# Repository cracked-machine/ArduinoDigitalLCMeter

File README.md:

# ArduinoDigitalLCMeter
ArduinoNano-based Digital LC Meter with 2.42" OLED display

Based on this Silicon Chip magazine [article](Silicon Chip June 2017 p28-53.pdf)

### Schematic

https://github.com/cracked-machine/ArduinoDigitalLCMeter/blob/master/Hardware/docs/Digital_LC_Meter.pdf

### Layout

### Front Panel

### BOM

https://github.com/cracked-machine/ArduinoDigitalLCMeter/blob/master/Hardware/docs/Digital_LC_Meter.csv

* Carlingswitch Double Pole Double Throw (DPDT), Latching Rocker Switch Panel - Mfr. Part No. 621-1592900NXRS
* Marquardt Single Pole Double Throw (SPDT), (On)-Off-(On) Rocker Switch Panel - Mfr. Part No. 1808.1302
* APEM Single Pole Single Throw (SPST) Momentary Push Button Switch, Panel Mount - Mfr. Part No. 1213C RED
* www.diymore.cc 2.42" Inch 12864 OLED Display Module SSD1309

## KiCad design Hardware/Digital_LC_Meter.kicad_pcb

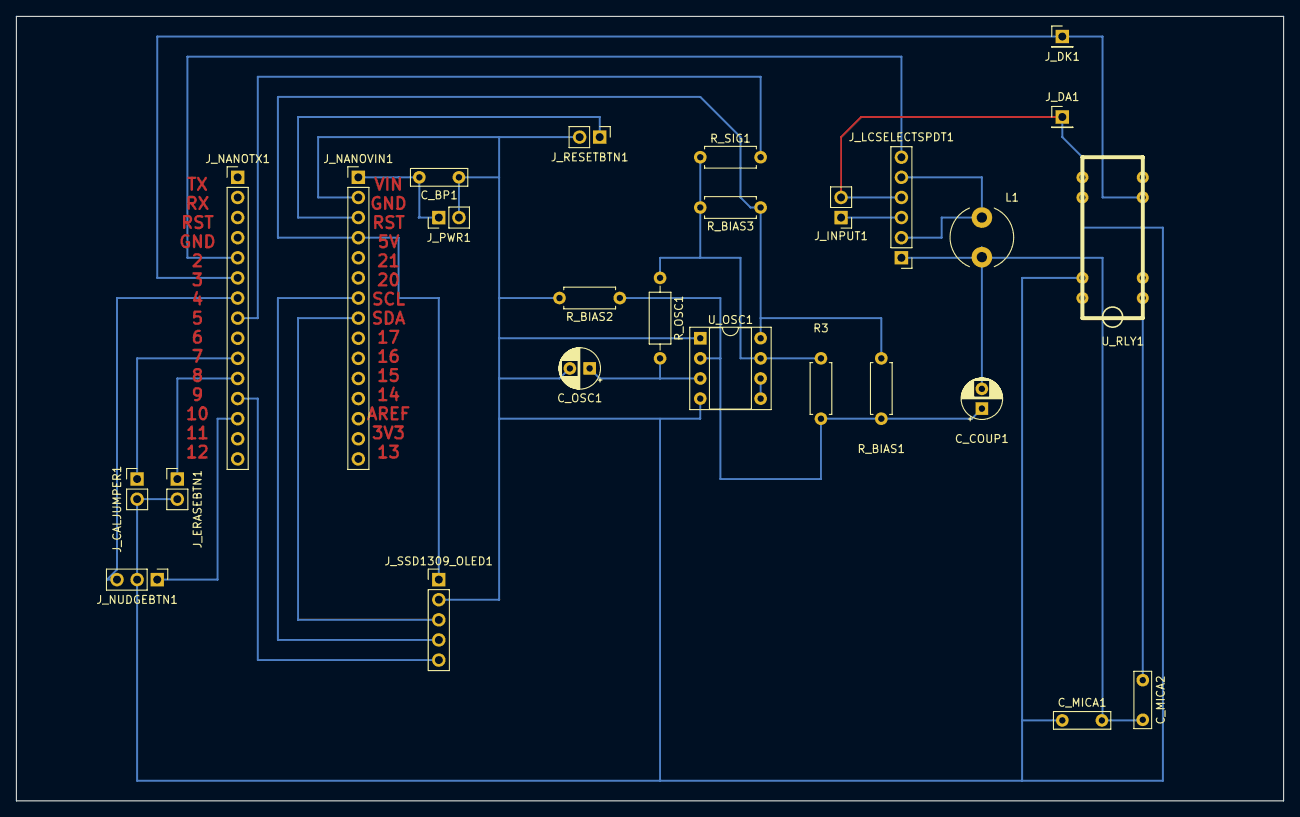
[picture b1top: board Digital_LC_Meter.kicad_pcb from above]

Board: 2 copper layers, 160.0 x 99.1 mm, 26 parts (0 on the bottom side), 22 nets.

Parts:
C_BP1: 100nF; C_Rect_L7.0mm_W2.0mm_P5.00mm
C_COUP1: 10uF; CP_Radial_D5.0mm_P2.50mm
C_MICA1, C_MICA2: 1nF; C_Rect_L7.0mm_W2.0mm_P5.00mm
C_OSC1: 10uF; CP_Radial_D5.0mm_P2.50mm
J_CALJUMPER1: Conn_01x02; PinHeader_1x02_P2.54mm_Vertical
J_DA1: Conn_01x01; PinHeader_1x01_P2.54mm_Vertical
J_DK1: Conn_01x01; PinHeader_1x01_P2.54mm_Vertical
J_ERASEBTN1: Conn_01x02; PinHeader_1x02_P2.54mm_Vertical
J_INPUT1: Conn_01x02; PinHeader_1x02_P2.54mm_Vertical
J_LCSELECTSPDT1: Conn_01x06; PinHeader_1x06_P2.54mm_Vertical
J_NANOTX1: Conn_01x15; PinHeader_1x15_P2.54mm_Vertical
J_NANOVIN1: Conn_01x15; PinHeader_1x15_P2.54mm_Vertical
J_NUDGEBTN1: Conn_01x03; PinHeader_1x03_P2.54mm_Vertical
J_PWR1: Conn_01x02; PinHeader_1x02_P2.54mm_Vertical
J_RESETBTN1: Conn_01x02; PinHeader_1x02_P2.54mm_Vertical
J_SSD1309_OLED1: Conn_01x05; PinHeader_1x05_P2.54mm_Vertical
L1: 100uH; L_Radial_D7.8mm_P5.00mm_Fastron_07HCP
R3: 100K; R_Axial_DIN0207_L6.3mm_D2.5mm_P7.62mm_Horizontal
R_BIAS1, R_BIAS2: 100K; R_Axial_DIN0207_L6.3mm_D2.5mm_P7.62mm_Horizontal
R_BIAS3: 4K7; R_Axial_DIN0207_L6.3mm_D2.5mm_P7.62mm_Horizontal
R_OSC1: 47K; R_Axial_DIN0207_L6.3mm_D2.5mm_P10.16mm_Horizontal
R_SIG1: 6K8; R_Axial_DIN0207_L6.3mm_D2.5mm_P7.62mm_Horizontal
U_OSC1: LM311; DIP-8_W7.62mm_Socket
U_RLY1: TE_ReedRelay_V23100V4xxxA010; TE_ReedRelay_V23100V4

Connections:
/5V: J_NANOVIN1.4, J_SSD1309_OLED1.1, R_BIAS1.1, R_BIAS3.1, U_OSC1.8
/CAL_ERASE_PIN8: J_ERASEBTN1.1, J_NANOTX1.11
/CAL_LK_PIN7: J_CALJUMPER1.1, J_NANOTX1.10
/CL_BAR_PIN2: J_LCSELECTSPDT1.6, J_NANOTX1.5
/DECR_PIN4: J_NANOTX1.7, J_NUDGEBTN1.3
/GND: C_BP1.1, C_MICA1.1, C_OSC1.2, J_CALJUMPER1.2, J_DA1.1, J_ERASEBTN1.2, J_INPUT1.2, J_LCSELECTSPDT1.4, J_NANOVIN1.2, J_NUDGEBTN1.2, J_PWR1.2, J_RESETBTN1.2, J_SSD1309_OLED1.2, R_BIAS2.2, U_OSC1.1, U_OSC1.4, U_RLY1.8, U_RLY1.9, U_RLY1.13
/INCR_PIN10: J_NANOTX1.13, J_NUDGEBTN1.1
/IND_PARALLEL: C_COUP1.2, C_MICA1.2, C_MICA2.2, J_LCSELECTSPDT1.1, L1.2
/IND_SERIES: J_LCSELECTSPDT1.2, J_LCSELECTSPDT1.5, L1.1
/OSC_SIG_PIN5: J_NANOTX1.8, R_SIG1.2
/RELAY_PIN3: J_DK1.1, J_NANOTX1.6, U_RLY1.6
/RESET_PIN: J_NANOVIN1.3, J_RESETBTN1.1
/SCL: J_NANOVIN1.7, J_SSD1309_OLED1.4
/SDA: J_NANOVIN1.8, J_SSD1309_OLED1.3
/SRST: J_NANOTX1.12, J_SSD1309_OLED1.5
/VIN: C_BP1.2, J_NANOVIN1.1, J_PWR1.1
unnamed: C_COUP1.1, R3.2, R_BIAS1.2, R_BIAS2.1, U_OSC1.2
unnamed: C_MICA2.1, U_RLY1.1
unnamed: C_OSC1.1, R_OSC1.2, U_OSC1.3
unnamed: J_INPUT1.1, J_LCSELECTSPDT1.3
unnamed: R3.1, R_BIAS3.2, R_OSC1.1, R_SIG1.1, U_OSC1.7
unnamed: U_OSC1.5, U_OSC1.6

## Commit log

2018-09-11 Converted schematic to KicadV5
2018-09-12 updated kicad files
2018-09-12 software update
2018-09-12 Added 2nd OLED and TCA9548A IICMux. Updated Schematic and Board Layouts
2018-09-14 updates
    - Added I2C Mux (TCA9548A) to design
    - Initial prototype tested (firmware needs work)
    - Created Front Panel Template for enclosure (Hammond 1455T1601)
2018-09-19 fixed OLED screen wiring on prototype, updated schematic and layout
2018-09-19 updated docs
2018-09-21 updated firmware
    Added pin interrupts for nudge
2018-09-22 updated SW
    - Fixed EEPROM updates issues. Cal Settings now preserved after restart.
2018-09-22 updated software
    - Fixed display graphics
2022-12-06 added article containing block diagram and theory of operation
2022-12-06 added gitignore
